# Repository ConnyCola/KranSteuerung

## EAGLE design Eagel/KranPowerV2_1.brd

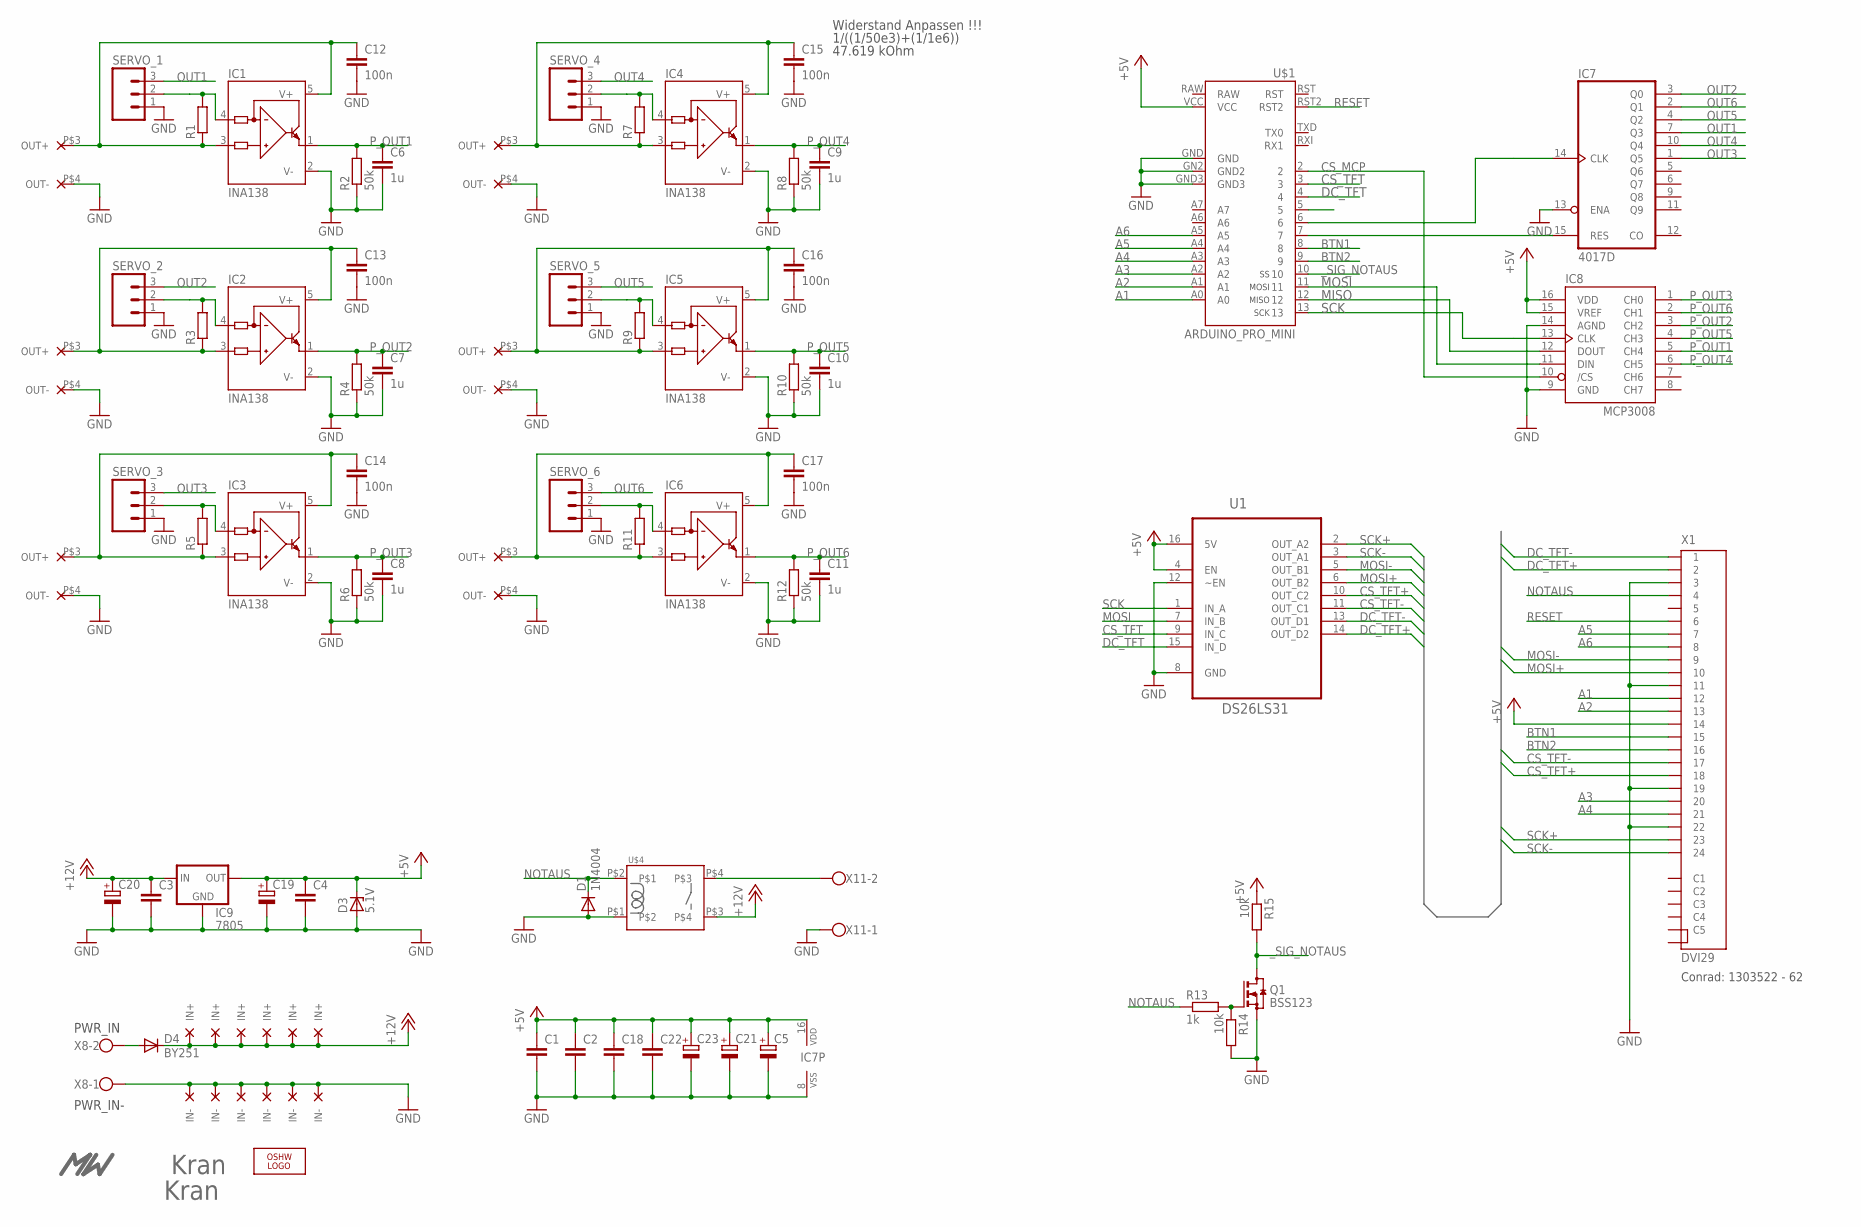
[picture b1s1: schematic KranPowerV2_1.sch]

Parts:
C1, C2, C3, C4, C18, C22: C-EUC0603; C0603
C5, C19, C20, C21, C23: CPOL-EUSMCB; SMC_B
C6, C7, C8, C9, C10, C11: 1u; C0603
C12, C13, C14, C15, C16, C17: 100n; C0603
D1: 1N4004; DO41-10
D3: 5.1V; DO34Z7
D4: BY251; DO201-15
IC1, IC2, IC3, IC4, IC5, IC6: INA138; SOT23-5
IC7: 4017D; SO16
IC8: MCP3008; SO16
IC9: 7805; 78XXL
LOGO1: OSHW_LOGO_FILLX0350-NT; OSHW_FILLX350_NOTEXT
Q1: BSS123; SOT23
R1, R3, R5, R7, R9, R11: R-EU_R2512; R2512
R2, R4, R6, R8, R10, R12: 50k; R0603
R13: 1k; R0603
R14, R15: 10k; R0603
SERVO_1, SERVO_2, SERVO_3, SERVO_4, SERVO_5, SERVO_6: M03LOCK; 1X03_LOCK
U1: DS26LS31; SOIC127P600X175-16N
U$1: ARDUINO_PRO_MINI
U$2: MW_LOGO; MW_11X5MM
U$3, U$13: KRAN_LOGO
U$4: RELAY_ZETTLER_AZ767
U$5, U$6, U$7, U$8, U$9, U$10: LM2596_STEPDOWN
X1: DVI29; CCDVI-29DVISIR-A-2
X8, X11: W237-102

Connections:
+5V: C1.1, C2.1, C4.1, C5.+, C18.1, C19.+, C21.+, C22.1, C23.+, D3.C, IC7.16 (VDD), IC8.15 (VREF), IC8.16 (VDD), IC9.OUT, R15.1, U1.4 (EN), U1.16 (5V), U$1.VCC, X1.14
+12V: C3.1, C20.+, D4.C, IC9.IN, U$4.P$3, U$5.P$1 (IN+), U$6.P$1 (IN+), U$7.P$1 (IN+), U$8.P$1 (IN+), U$9.P$1 (IN+), U$10.P$1 (IN+)
A1: U$1.A0, X1.12
A2: U$1.A1, X1.13
A3: U$1.A2, X1.20
A4: U$1.A3, X1.21
A5: U$1.A4, X1.7
A6: U$1.A5, X1.8
BTN1: U$1.8, X1.15
BTN2: U$1.9, X1.16
CS_MCP: IC8.10 (/CS), U$1.2
CS_TFT: U1.9 (IN_C), U$1.3
CS_TFT+: U1.10 (OUT_C2), X1.18
CS_TFT-: U1.11 (OUT_C1), X1.17
DC_TFT: U1.15 (IN_D), U$1.4
DC_TFT+: U1.14 (OUT_D2), X1.2
DC_TFT-: U1.13 (OUT_D1), X1.1
GND: C1.2, C2.2, C3.2, C4.2, C5.-, C6.2, C7.2, C8.2, C9.2, C10.2, C11.2, C12.2, C13.2, C14.2, C15.2, C16.2, C17.2, C18.2, C19.-, C20.-, C21.-, C22.2, C23.-, D1.A, D3.A, IC1.2 (V-), IC2.2 (V-), IC3.2 (V-), IC4.2 (V-), IC5.2 (V-), IC6.2 (V-), IC7.8 (VSS), IC7.13 (ENA), IC8.9 (GND), IC8.14 (AGND), IC9.GND, Q1.2 (S), R2.1, R4.1, R6.1, R8.1, R10.1, R12.1, R14.2, SERVO_1.1, SERVO_2.1, SERVO_3.1, SERVO_4.1, SERVO_5.1, SERVO_6.1, U1.8 (GND), U1.12 (~EN), U$1.GN2 (GND2), U$1.GND, U$1.GND3, U$4.P$1, U$5.P$2 (IN-), U$5.P$4 (OUT-), U$6.P$2 (IN-), U$6.P$4 (OUT-), U$7.P$2 (IN-), U$7.P$4 (OUT-), U$8.P$2 (IN-), U$8.P$4 (OUT-), U$9.P$2 (IN-), U$9.P$4 (OUT-), U$10.P$2 (IN-), U$10.P$4 (OUT-), X1.3, X1.11, X1.19, X1.22, X8.1, X11.1
MISO: IC8.12 (DOUT), U$1.12
MOSI: IC8.11 (DIN), U1.7 (IN_B), U$1.11
MOSI+: U1.6 (OUT_B2), X1.10
MOSI-: U1.5 (OUT_B1), X1.9
unnamed: C12.1, IC1.3 (IN+), IC1.5 (V+), R1.1, U$5.P$3 (OUT+)
unnamed: IC1.4 (IN-), R1.2, SERVO_1.2
unnamed: C13.1, IC2.3 (IN+), IC2.5 (V+), R3.1, U$6.P$3 (OUT+)
unnamed: IC2.4 (IN-), R3.2, SERVO_2.2
unnamed: C14.1, IC3.3 (IN+), IC3.5 (V+), R5.1, U$7.P$3 (OUT+)
unnamed: IC3.4 (IN-), R5.2, SERVO_3.2
unnamed: C15.1, IC4.3 (IN+), IC4.5 (V+), R7.1, U$8.P$3 (OUT+)
unnamed: IC4.4 (IN-), R7.2, SERVO_4.2
unnamed: C16.1, IC5.3 (IN+), IC5.5 (V+), R9.1, U$9.P$3 (OUT+)
unnamed: IC5.4 (IN-), R9.2, SERVO_5.2
unnamed: C17.1, IC6.3 (IN+), IC6.5 (V+), R11.1, U$10.P$3 (OUT+)
unnamed: IC6.4 (IN-), R11.2, SERVO_6.2
unnamed: D4.A, X8.2
unnamed: IC7.14 (CLK), U$1.6
unnamed: IC7.15 (RES), U$1.7
unnamed: Q1.1 (G), R13.2, R14.1
unnamed: U$4.P$4, X11.2
NOTAUS: D1.C, R13.1, U$4.P$2, X1.4
OUT1: IC7.7 (Q3), SERVO_1.3
OUT2: IC7.3 (Q0), SERVO_2.3
OUT3: IC7.1 (Q5), SERVO_3.3
OUT4: IC7.10 (Q4), SERVO_4.3
OUT5: IC7.4 (Q2), SERVO_5.3
OUT6: IC7.2 (Q1), SERVO_6.3
P_OUT1: C6.1, IC1.1 (OUT), IC8.5 (CH4), R2.2
P_OUT2: C7.1, IC2.1 (OUT), IC8.3 (CH2), R4.2
P_OUT3: C8.1, IC3.1 (OUT), IC8.1 (CH0), R6.2
P_OUT4: C9.1, IC4.1 (OUT), IC8.6 (CH5), R8.2
P_OUT5: C10.1, IC5.1 (OUT), IC8.4 (CH3), R10.2
P_OUT6: C11.1, IC6.1 (OUT), IC8.2 (CH1), R12.2
RESET: U$1.RST2, X1.6
SCK: IC8.13 (CLK), U1.1 (IN_A), U$1.13
SCK+: U1.2 (OUT_A2), X1.23
SCK-: U1.3 (OUT_A1), X1.24
_SIG_NOTAUS: Q1.3 (D), R15.2, U$1.10

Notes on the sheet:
1/((1/50e3)+(1/1e6))
47.619 kOhm
Widerstand Anpassen !!!
PWR_IN
PWR_IN-
Conrad: 1303522 - 62

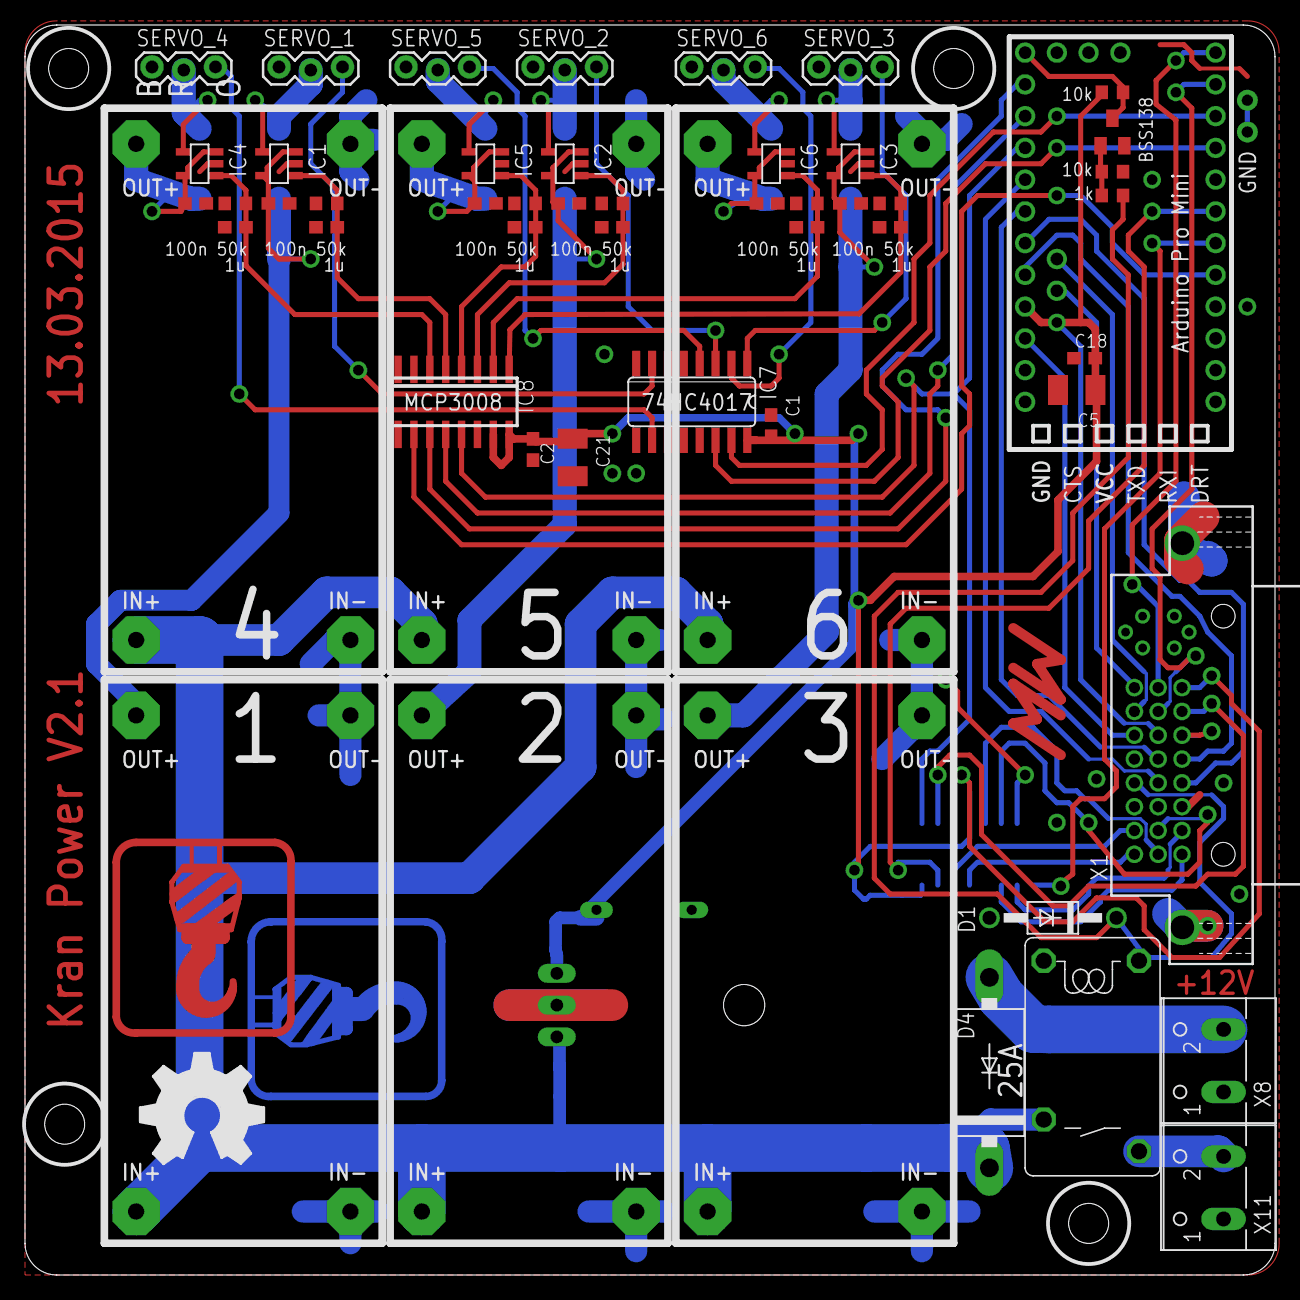
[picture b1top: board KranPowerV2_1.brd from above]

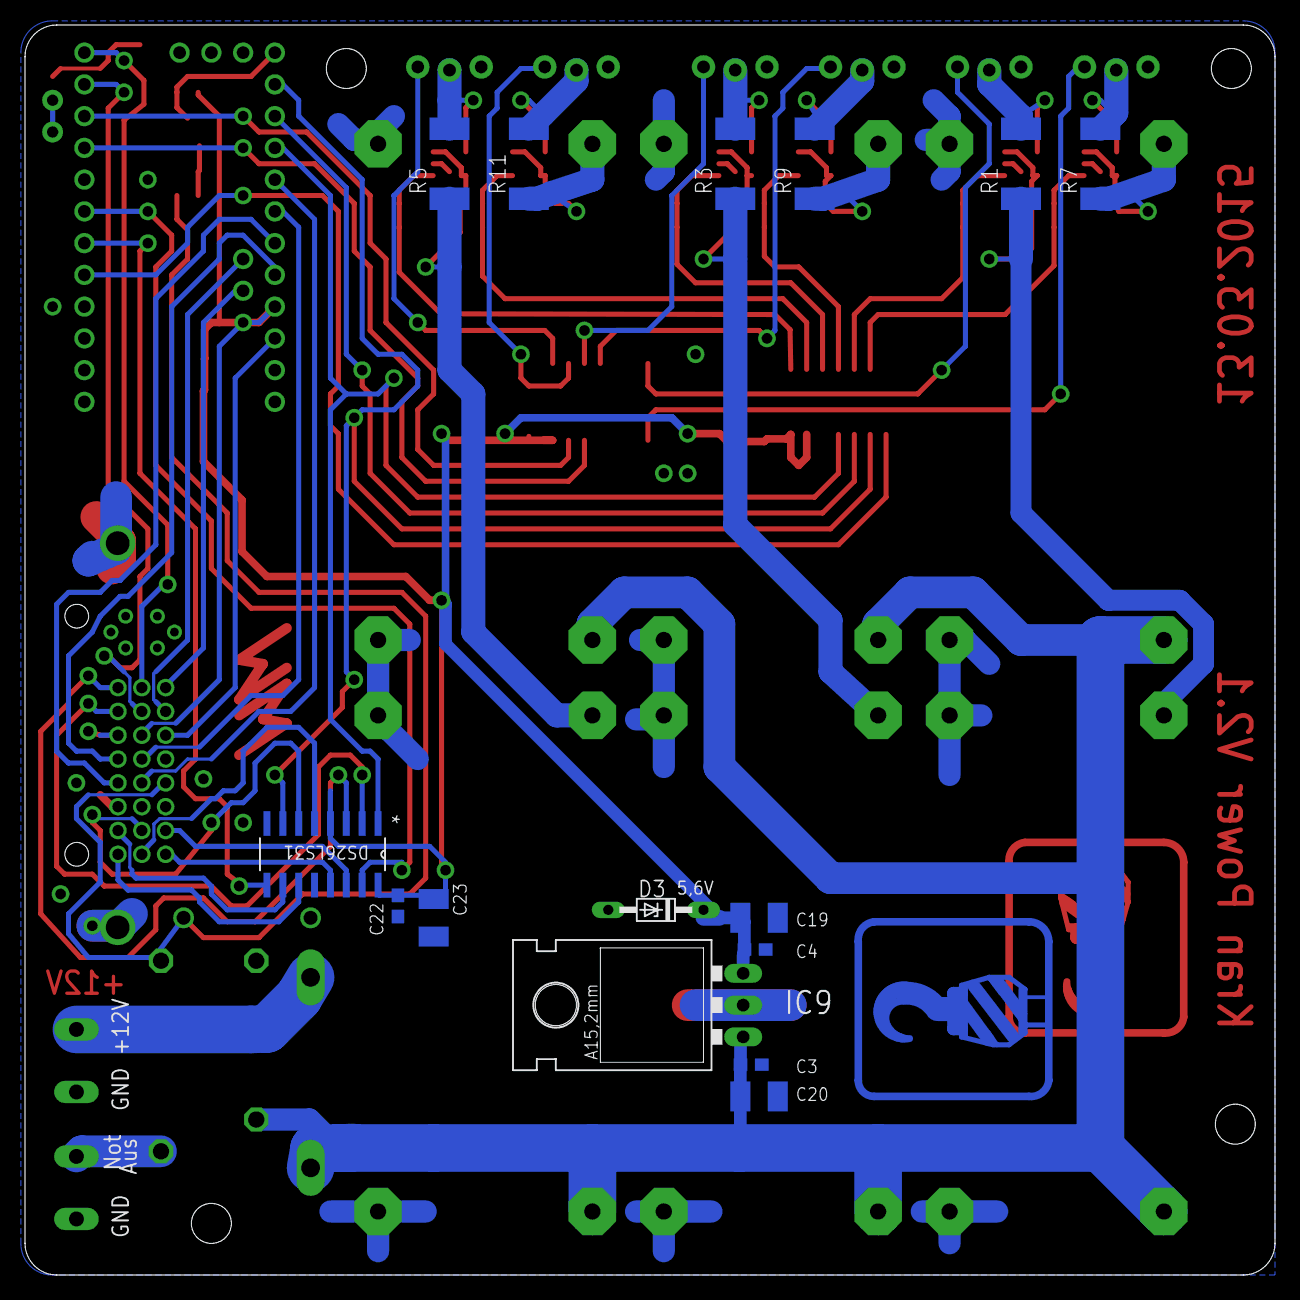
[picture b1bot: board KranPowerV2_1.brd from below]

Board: 2 copper layers, 100.0 x 100.0 mm, 76 parts (17 on the bottom side), 57 nets.

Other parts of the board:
U$11: MW_11X5MM_SOLDER
U$12, U$14: KRAN_LOGO_STOP

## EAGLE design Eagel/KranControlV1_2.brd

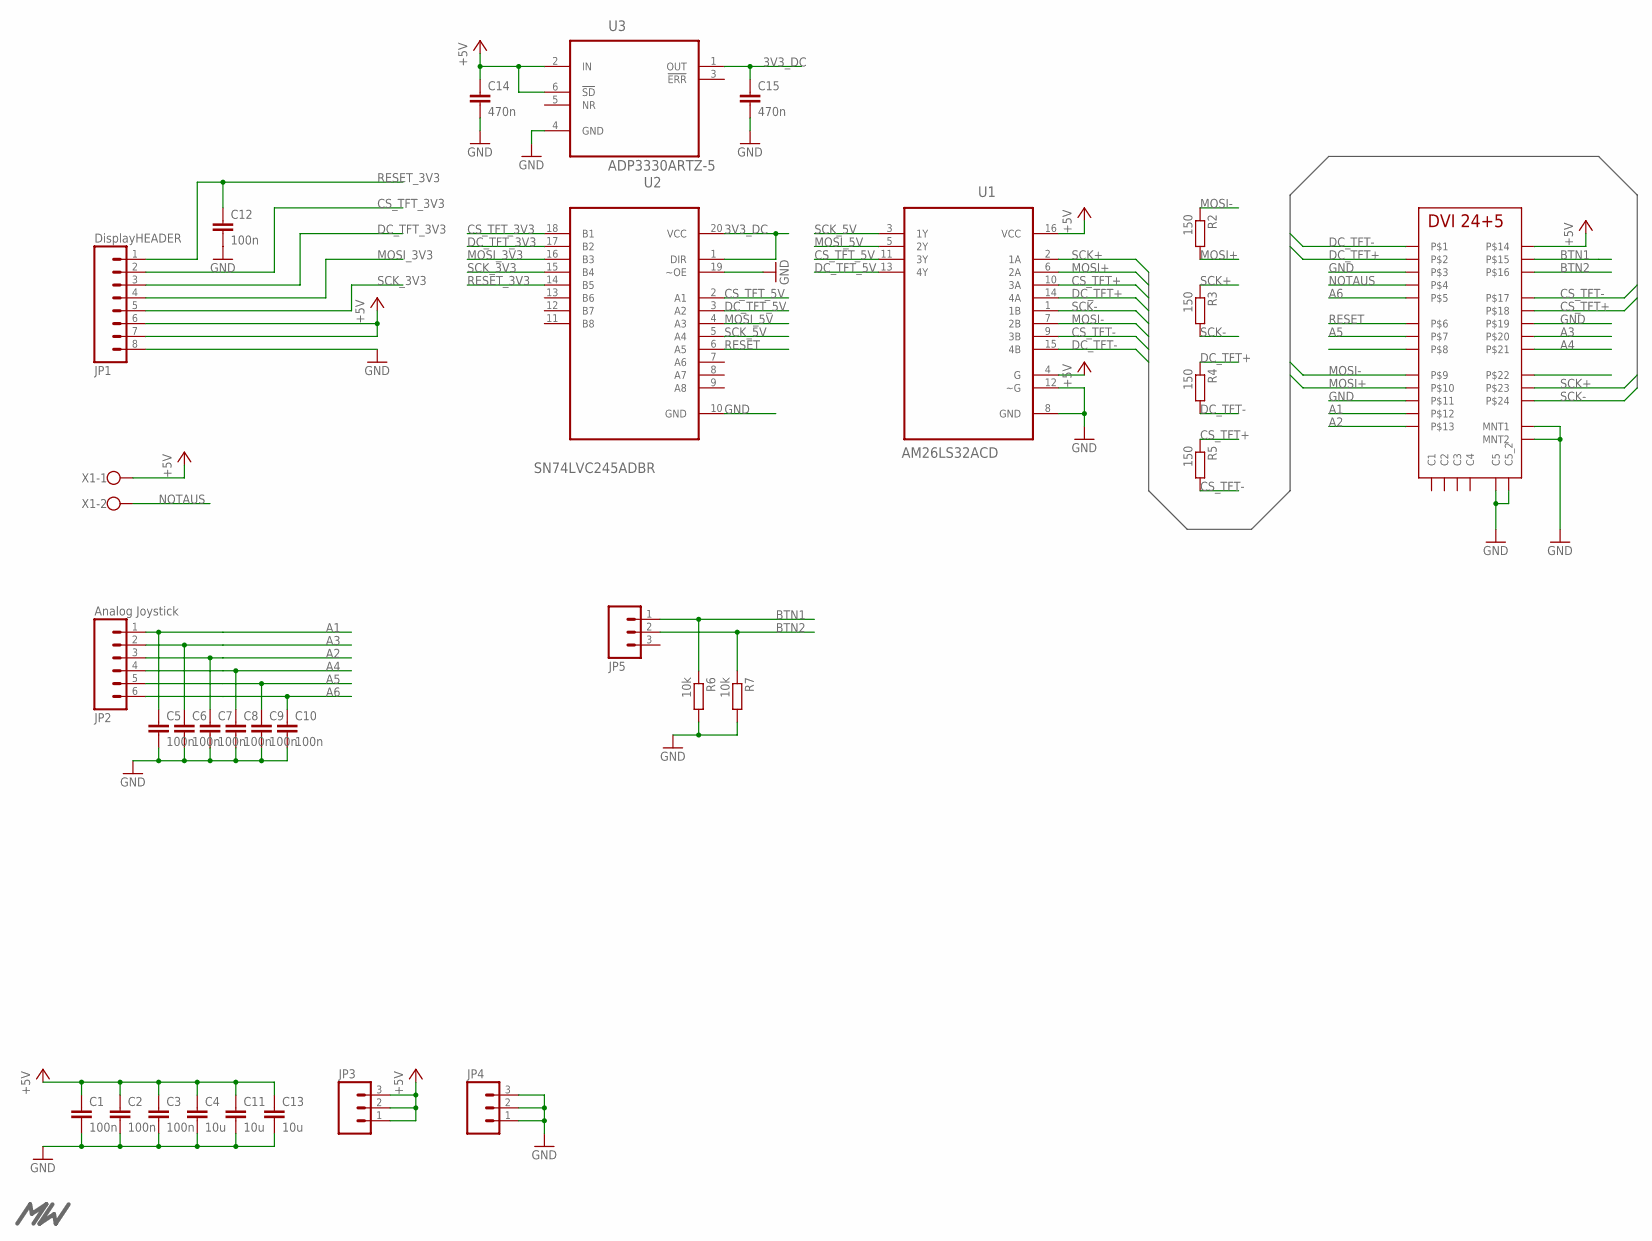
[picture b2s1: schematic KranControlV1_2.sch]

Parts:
C1, C2, C3, C5, C6, C7, C8, C9, C10, C12: 100n; C0603
C4, C11, C13: 10u; C1206
C14, C15: 470n; C0603
JP1: DisplayHEADER; 1X08_LOCK
JP2: Analog Joystick; 1X06_FEMALE_LOCK.010
JP3, JP4, JP5: M03LOCK; 1X03_LOCK
R2, R3, R4, R5: 150; R0603
R6, R7: 10k; R0603
U1: AM26LS32ACD; SOIC127P600X175-16N
U2: SN74LVC245ADBR; SOP65P780X200-20N
U3: ADP3330ARTZ-5; SOT95P280X145-6N
U$1: DVI_BUCHSE
U$3: MW_LOGO; MW_11X5MM
X1: W237-102

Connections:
3V3_DC: C15.1, U2.1 (DIR), U2.20 (VCC), U3.1 (OUT)
+5V: C1.1, C2.1, C3.1, C4.1, C11.1, C13.1, C14.1, JP1.6, JP1.7, JP3.1, JP3.2, JP3.3, U1.4 (G), U1.16 (VCC), U3.2 (IN), U3.6 (!SD), U$1.P$14, X1.1
A1: C5.1, JP2.1, U$1.P$12
A2: C7.1, JP2.3, U$1.P$13
A3: C6.1, JP2.2, U$1.P$4
A4: C8.1, JP2.4, U$1.P$5
A5: C9.1, JP2.5, U$1.P$23
A6: C10.1, JP2.6, U$1.P$21
BTN1: JP5.1, R6.1, U$1.P$15
BTN2: JP5.2, R7.1, U$1.P$16
CS_TFT+: R5.1, U1.10 (3A), U$1.P$2
CS_TFT-: R5.2, U1.9 (3B), U$1.P$1
CS_TFT_3V3: JP1.2, U2.18 (B1)
CS_TFT_5V: U1.11 (3Y), U2.2 (A1)
DC_TFT+: R4.1, U1.14 (4A), U$1.P$18
DC_TFT-: R4.2, U1.15 (4B), U$1.P$17
DC_TFT_3V3: JP1.3, U2.17 (B2)
DC_TFT_5V: U1.13 (4Y), U2.3 (A2)
GND: C1.2, C2.2, C3.2, C4.2, C5.2, C6.2, C7.2, C8.2, C9.2, C10.2, C11.2, C12.2, C13.2, C14.2, C15.2, JP1.8, JP4.1, JP4.2, JP4.3, R6.2, R7.2, U1.8 (GND), U1.12 (~G), U2.10 (GND), U2.19 (~OE), U3.4 (GND), U$1.MNT1, U$1.MNT2, U$1.P$3, U$1.P$11, U$1.P$19, U$1.P$28 (C5), U$1.P$30 (C5_2)
MOSI+: R2.2, U1.6 (2A), U$1.P$10
MOSI-: R2.1, U1.7 (2B), U$1.P$9
MOSI_3V3: JP1.4, U2.16 (B3)
MOSI_5V: U1.5 (2Y), U2.4 (A3)
NOTAUS: U$1.P$20, X1.2
RESET: U2.6 (A5), U$1.P$22
RESET_3V3: C12.1, JP1.1, U2.14 (B5)
SCK+: R3.1, U1.2 (1A), U$1.P$7
SCK-: R3.2, U1.1 (1B), U$1.P$8
SCK_3V3: JP1.5, U2.15 (B4)
SCK_5V: U1.3 (1Y), U2.5 (A4)

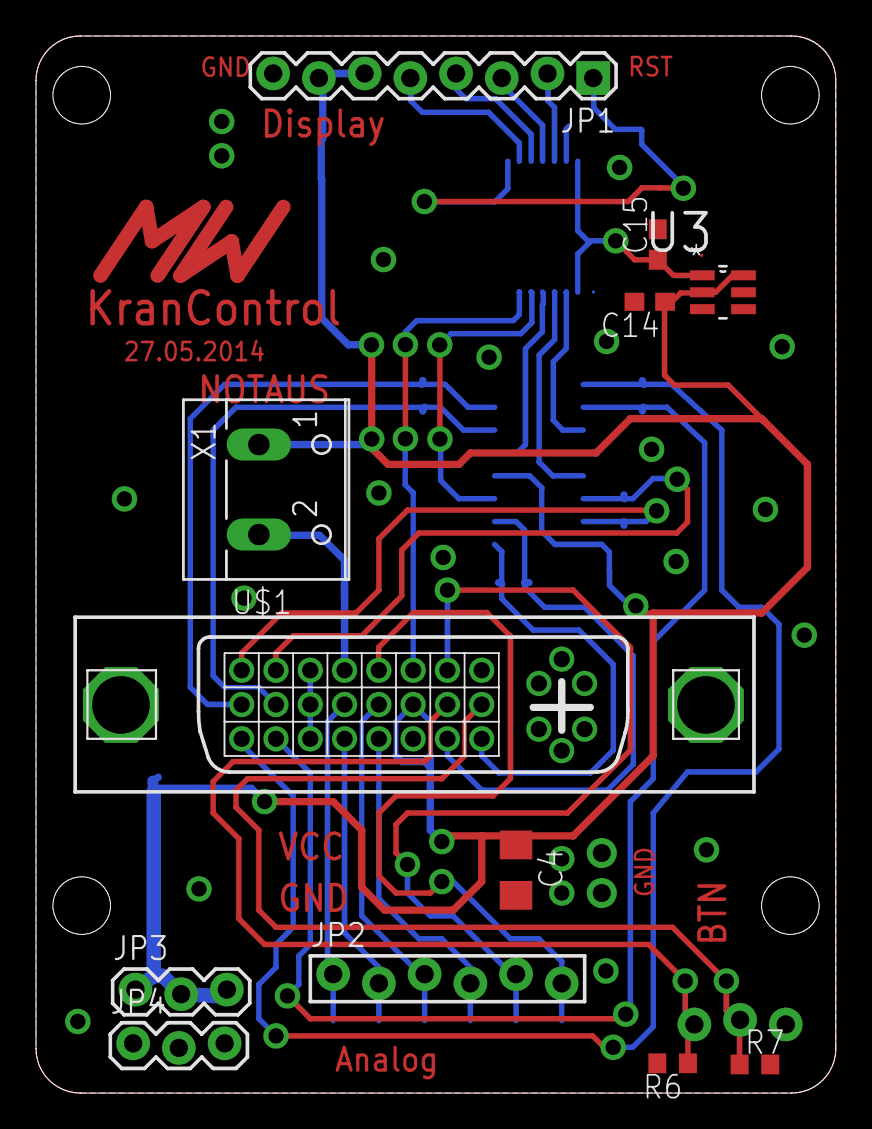
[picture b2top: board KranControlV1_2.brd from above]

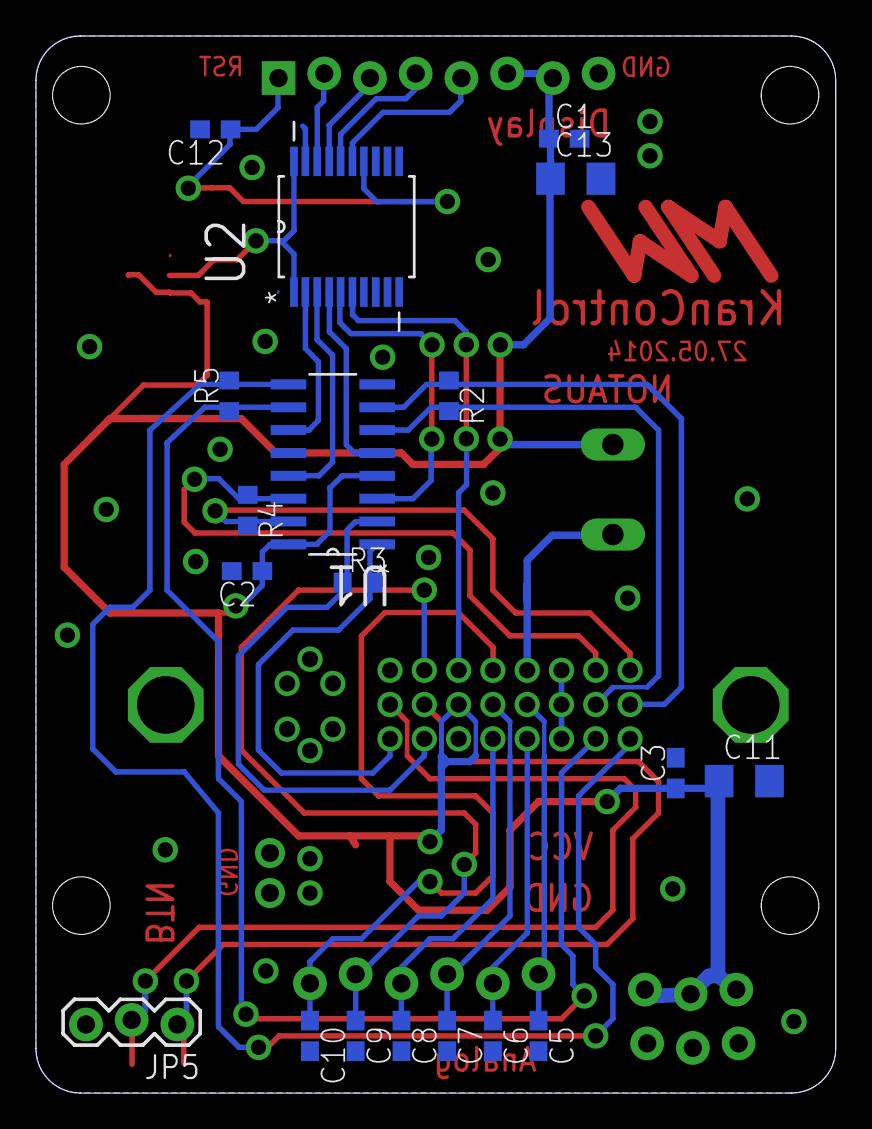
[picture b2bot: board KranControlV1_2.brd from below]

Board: 2 copper layers, 44.4 x 58.7 mm, 32 parts (19 on the bottom side), 30 nets.

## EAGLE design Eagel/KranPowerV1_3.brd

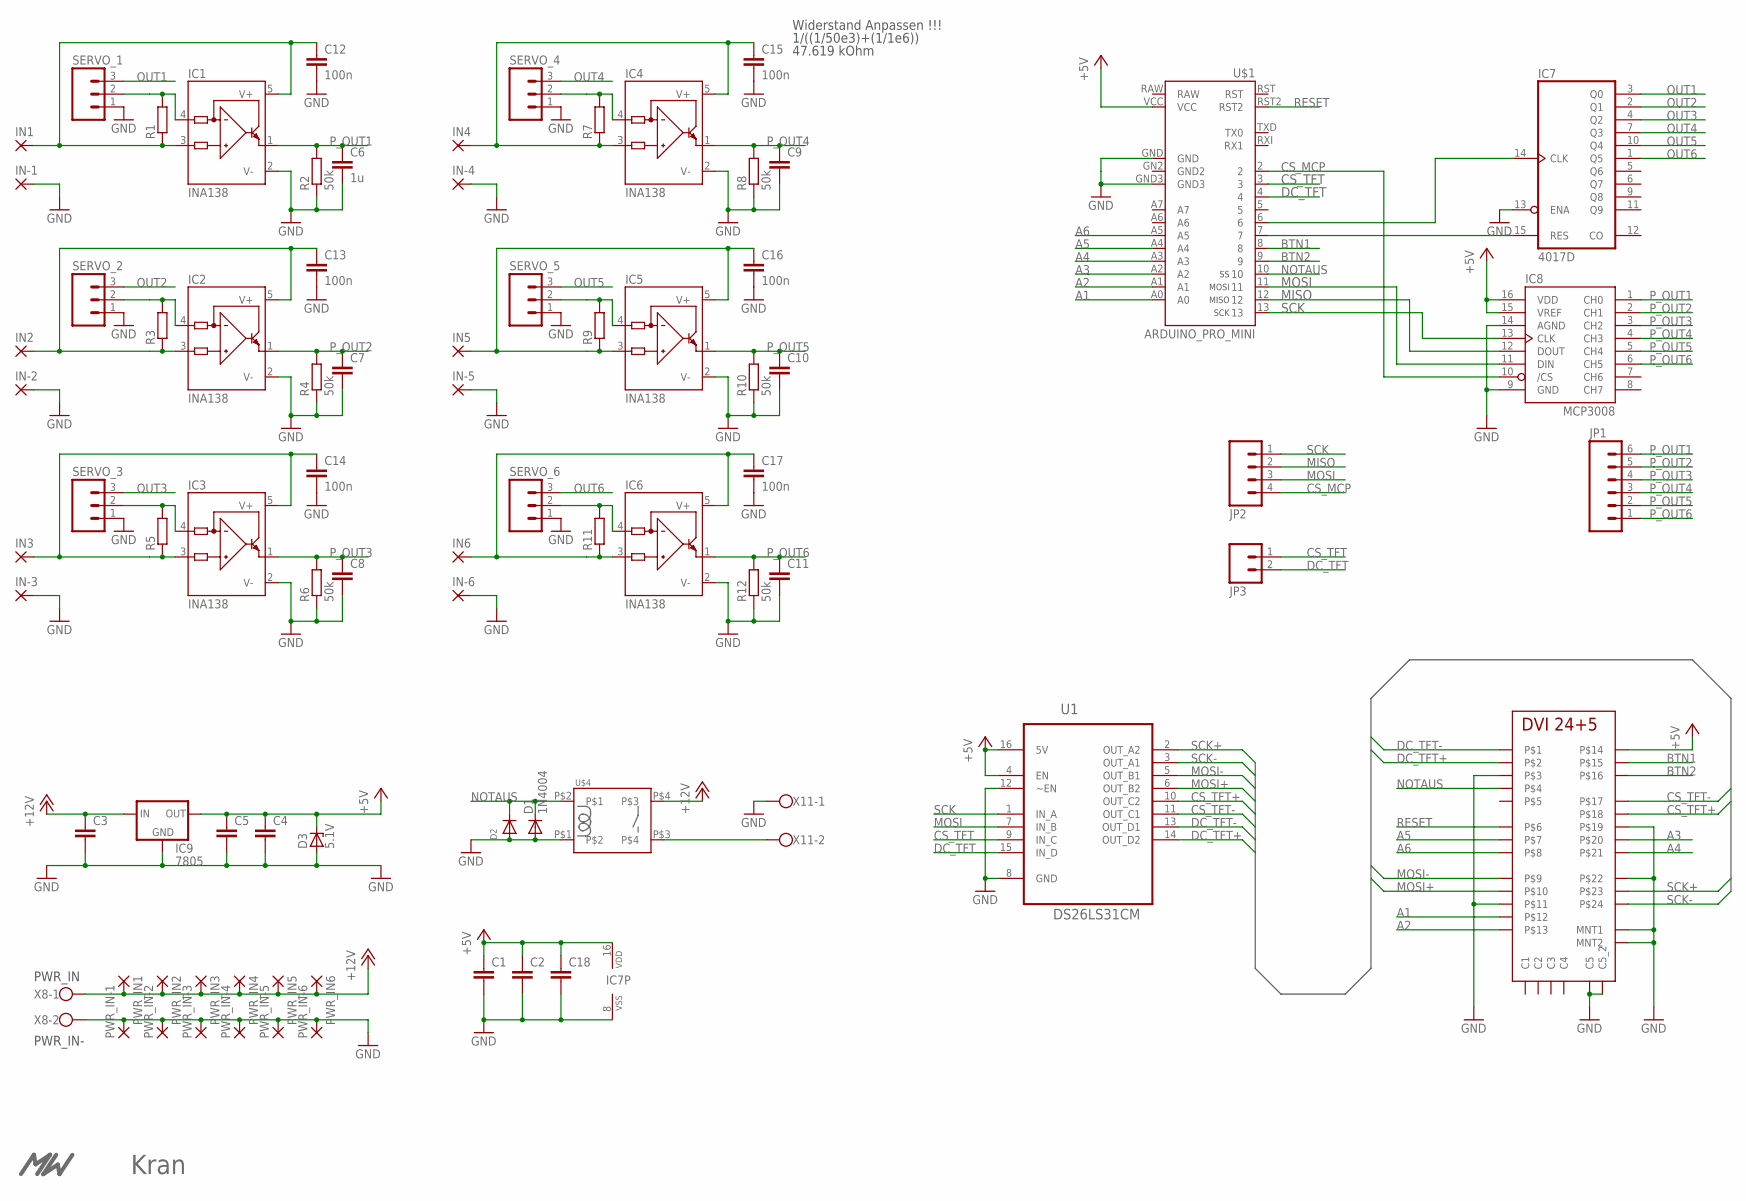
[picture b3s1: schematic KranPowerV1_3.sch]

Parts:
C1, C2, C3, C4, C7, C8, C9, C10, C11, C18: C-EUC0603; C0603
C5: C-EUC1206; C1206
C6: 1u; C0603
C12, C13, C14, C15, C16, C17: 100n; C0603
D1: 1N4004; DO41-10
D2: DIODESMA; SMADIODE
D3: 5.1V; DO34Z7
IC1, IC2, IC3, IC4, IC5, IC6: INA138; SOT23-5
IC7: 4017D; SO16
IC8: MCP3008; SO16
IC9: 7805; 78XXL
IN1, IN2, IN3, IN4, IN5, IN6: 3,81/1,3
IN-1, IN-2, IN-3, IN-4, IN-5, IN-6: 3,81/1,3
JP1: M06LOCK; 1X06_LOCK
JP2: M04LOCK; 1X04_LOCK
JP3: M02LOCK; 1X02_LOCK
PWR_IN1, PWR_IN2, PWR_IN3, PWR_IN4, PWR_IN5, PWR_IN6: 3,81/1,3
PWR_IN-1, PWR_IN-2, PWR_IN-3, PWR_IN-4, PWR_IN-5, PWR_IN-6: 3,81/1,3
R1, R3, R5, R7, R9, R11: R-EU_R2512; R2512
R2, R4, R6, R8, R10, R12: 50k; R0603
SERVO_1, SERVO_2, SERVO_3, SERVO_4, SERVO_5, SERVO_6: M03LOCK; 1X03_LOCK
U1: DS26LS31CM; SOIC127P600X175-16N
U$1: ARDUINO_PRO_MINI
U$2: MW_LOGO; MW_11X5MM
U$3: KRAN_LOGO
U$4: RELAY_ZETTLER_AZ767
U$11: DVI_BUCHSE
X8, X11: W237-102

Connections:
+5V: C1.1, C2.1, C4.1, C5.1, C18.1, D3.C, IC7.16 (VDD), IC8.15 (VREF), IC8.16 (VDD), IC9.OUT, U1.4 (EN), U1.16 (5V), U$1.VCC, U$11.P$14
+12V: C3.1, IC9.IN, PWR_IN1.1, PWR_IN2.1, PWR_IN3.1, PWR_IN4.1, PWR_IN5.1, PWR_IN6.1, U$4.P$4, X8.1
A1: U$1.A0, U$11.P$12
A2: U$1.A1, U$11.P$13
A3: U$1.A2, U$11.P$4
A4: U$1.A3, U$11.P$5
A5: U$1.A4, U$11.P$23
A6: U$1.A5, U$11.P$24
BTN1: U$1.8, U$11.P$15
BTN2: U$1.9, U$11.P$16
CS_MCP: IC8.10 (/CS), JP2.4, U$1.2
CS_TFT: JP3.1, U1.9 (IN_C), U$1.3
CS_TFT+: U1.10 (OUT_C2), U$11.P$2
CS_TFT-: U1.11 (OUT_C1), U$11.P$1
DC_TFT: JP3.2, U1.15 (IN_D), U$1.4
DC_TFT+: U1.14 (OUT_D2), U$11.P$18
DC_TFT-: U1.13 (OUT_D1), U$11.P$17
GND: C1.2, C2.2, C3.2, C4.2, C5.2, C6.2, C7.2, C8.2, C9.2, C10.2, C11.2, C12.2, C13.2, C14.2, C15.2, C16.2, C17.2, C18.2, D1.A, D2.A, D3.A, IC1.2 (V-), IC2.2 (V-), IC3.2 (V-), IC4.2 (V-), IC5.2 (V-), IC6.2 (V-), IC7.8 (VSS), IC7.13 (ENA), IC8.9 (GND), IC8.14 (AGND), IC9.GND, IN-1.1, IN-2.1, IN-3.1, IN-4.1, IN-5.1, IN-6.1, PWR_IN-1.1, PWR_IN-2.1, PWR_IN-3.1, PWR_IN-4.1, PWR_IN-5.1, PWR_IN-6.1, R2.1, R4.1, R6.1, R8.1, R10.1, R12.1, SERVO_1.1, SERVO_2.1, SERVO_3.1, SERVO_4.1, SERVO_5.1, SERVO_6.1, U1.8 (GND), U1.12 (~EN), U$1.GND, U$1.GND3, U$4.P$1, U$11.MNT1, U$11.MNT2, U$11.P$3, U$11.P$6, U$11.P$11, U$11.P$19, U$11.P$28 (C5), U$11.P$30 (C5_2), X8.2, X11.1
MISO: IC8.12 (DOUT), JP2.2, U$1.12
MOSI: IC8.11 (DIN), JP2.3, U1.7 (IN_B), U$1.11
MOSI+: U1.6 (OUT_B2), U$11.P$10
MOSI-: U1.5 (OUT_B1), U$11.P$9
unnamed: C12.1, IC1.3 (IN+), IC1.5 (V+), IN1.1, R1.1
unnamed: IC1.4 (IN-), R1.2, SERVO_1.2
unnamed: C13.1, IC2.3 (IN+), IC2.5 (V+), IN2.1, R3.1
unnamed: IC2.4 (IN-), R3.2, SERVO_2.2
unnamed: C14.1, IC3.3 (IN+), IC3.5 (V+), IN3.1, R5.1
unnamed: IC3.4 (IN-), R5.2, SERVO_3.2
unnamed: C15.1, IC4.3 (IN+), IC4.5 (V+), IN4.1, R7.1
unnamed: IC4.4 (IN-), R7.2, SERVO_4.2
unnamed: C16.1, IC5.3 (IN+), IC5.5 (V+), IN5.1, R9.1
unnamed: IC5.4 (IN-), R9.2, SERVO_5.2
unnamed: C17.1, IC6.3 (IN+), IC6.5 (V+), IN6.1, R11.1
unnamed: IC6.4 (IN-), R11.2, SERVO_6.2
unnamed: IC7.14 (CLK), U$1.6
unnamed: IC7.15 (RES), U$1.7
unnamed: U$4.P$3, X11.2
NOTAUS: D1.C, D2.C, U$1.10, U$4.P$2, U$11.P$20
OUT1: IC7.3 (Q0), SERVO_1.3
OUT2: IC7.2 (Q1), SERVO_2.3
OUT3: IC7.4 (Q2), SERVO_3.3
OUT4: IC7.7 (Q3), SERVO_4.3
OUT5: IC7.10 (Q4), SERVO_5.3
OUT6: IC7.1 (Q5), SERVO_6.3
P_OUT1: C6.1, IC1.1 (OUT), IC8.1 (CH0), JP1.6, R2.2
P_OUT2: C7.1, IC2.1 (OUT), IC8.2 (CH1), JP1.5, R4.2
P_OUT3: C8.1, IC3.1 (OUT), IC8.3 (CH2), JP1.4, R6.2
P_OUT4: C9.1, IC4.1 (OUT), IC8.4 (CH3), JP1.3, R8.2
P_OUT5: C10.1, IC5.1 (OUT), IC8.5 (CH4), JP1.2, R10.2
P_OUT6: C11.1, IC6.1 (OUT), IC8.6 (CH5), JP1.1, R12.2
RESET: U$1.RST2, U$11.P$22
SCK: IC8.13 (CLK), JP2.1, U1.1 (IN_A), U$1.13
SCK+: U1.2 (OUT_A2), U$11.P$7
SCK-: U1.3 (OUT_A1), U$11.P$8

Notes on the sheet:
1/((1/50e3)+(1/1e6))
47.619 kOhm
Widerstand Anpassen !!!
PWR_IN
PWR_IN-

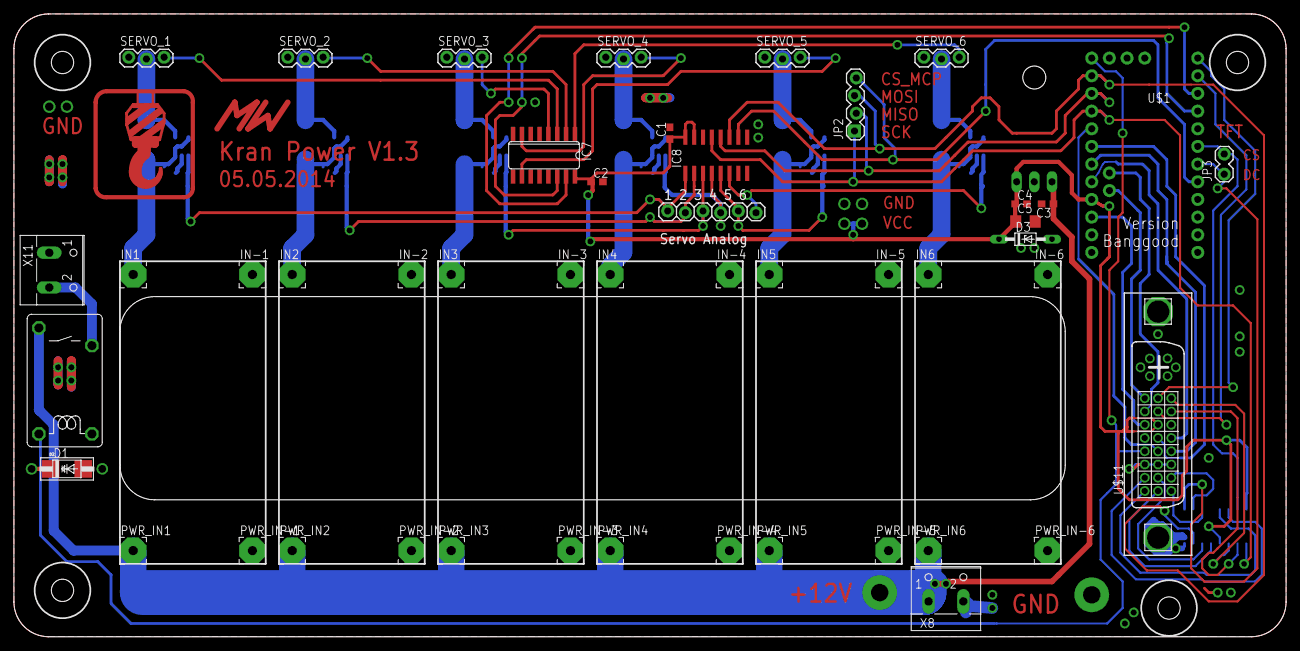
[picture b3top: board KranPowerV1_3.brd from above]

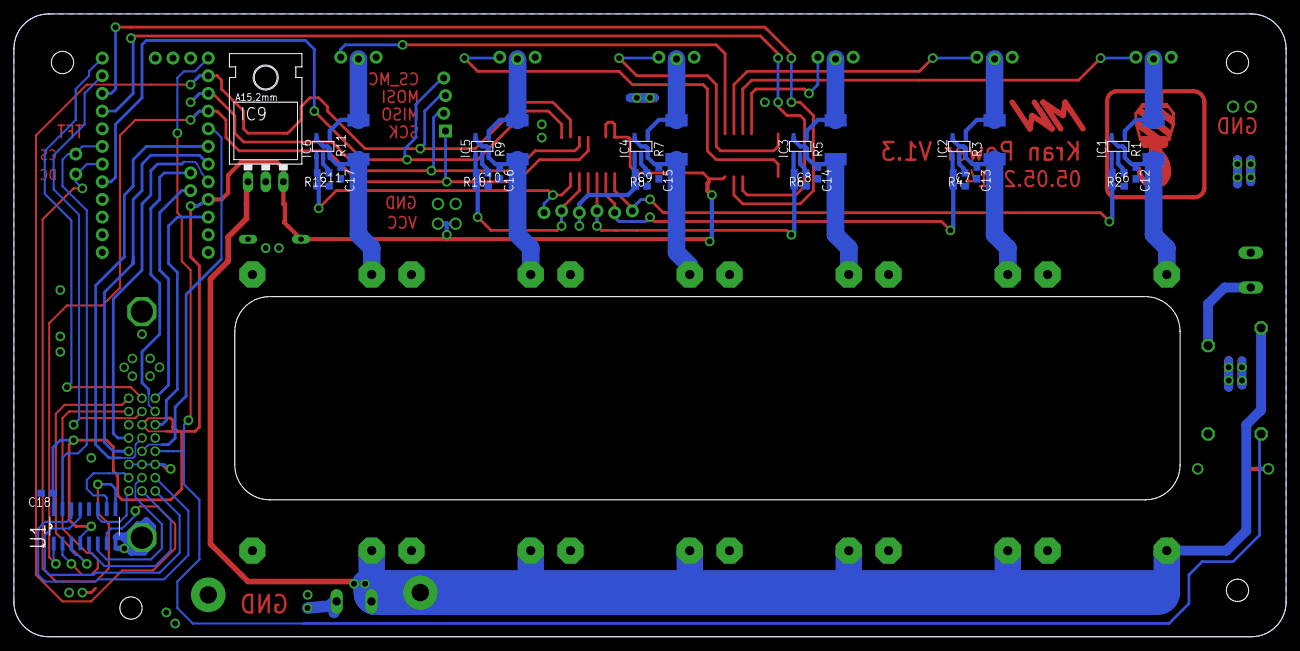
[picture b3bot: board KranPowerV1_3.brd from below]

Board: 2 copper layers, 182.9 x 89.5 mm, 83 parts (33 on the bottom side), 54 nets.

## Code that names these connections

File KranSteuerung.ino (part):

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
#define sclk 	13  // Don't change
#define mosi 	11  // Don't change
#define cs_tft	3   // 9
#define dc   	4   // 8
#define rst  	10   // 7  // you can also connect this to the Arduino reset

#define cs_mcp	2		// CS for MCP3008

#define BTN1	8		//Button 1 Pin
#define BTN2	9		//Button 2 Pin
#define NOTAUS  5		//NOTAUS PIN

#define BAL_HEI		50		//Hoehe des Balken
#define BAL_TOP		46		//Anfangspunkt der Balken (obere Kante)
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//***************
void setup(void) {

	pinMode(NOTAUS, INPUT);


	pinMode(BTN1, INPUT_PULLUP);
	pinMode(BTN2, INPUT_PULLUP);
		
	

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
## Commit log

2014-12-13 KranSteuerung
2014-12-13 eagle files
2015-03-30 V2_1 with Low Pass
    update to 100x100 pcb size + software implementation of a first order
    low pass
2015-04-10 small update
2016-02-16 Imported from https://ConnyCola@github.com/ConnyCola/KranSteuerung.git

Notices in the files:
parts and their libraries:
SparkFun: Licensing: CC v3.0 Share-Alike You are welcome to use this library for commercial purposes.
